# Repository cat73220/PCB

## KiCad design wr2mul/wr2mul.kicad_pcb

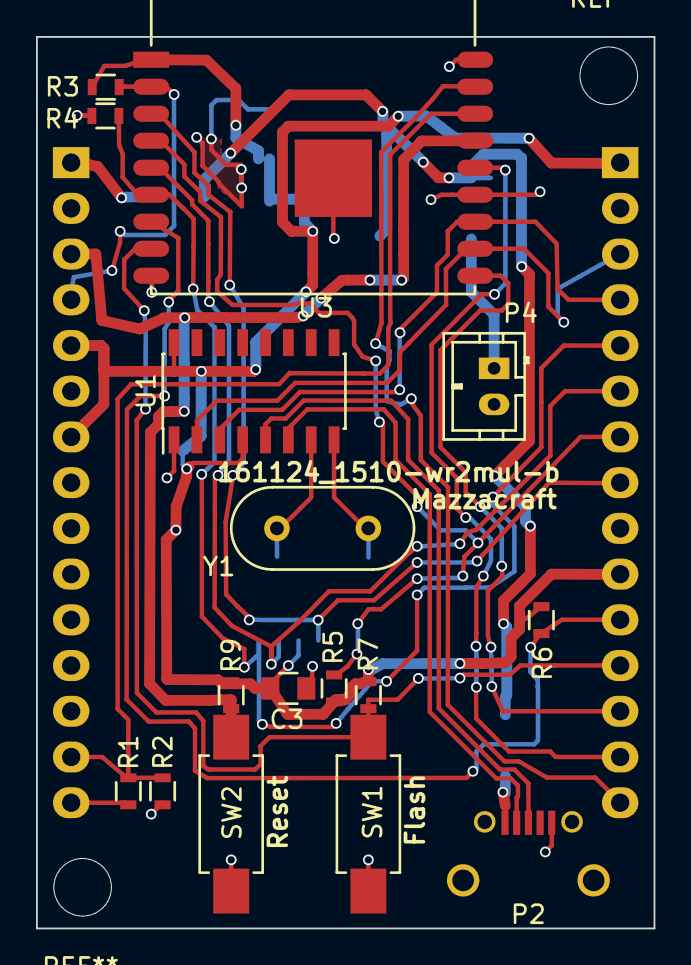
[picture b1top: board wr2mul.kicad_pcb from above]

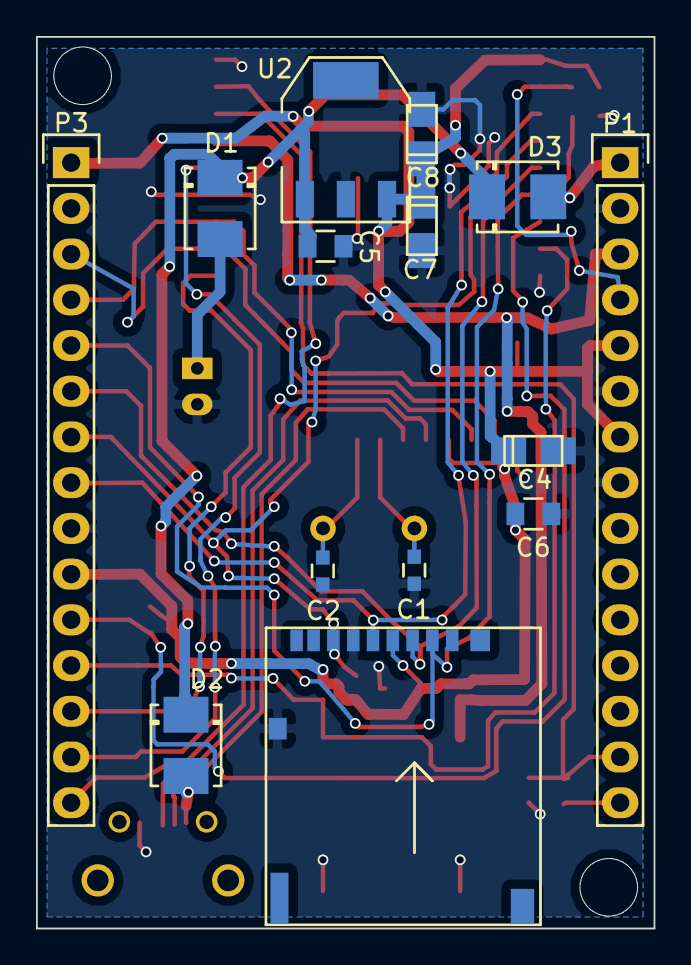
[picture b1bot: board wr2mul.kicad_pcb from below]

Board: 2 copper layers, 34.3 x 49.5 mm, 30 parts (14 on the bottom side), 25 nets.

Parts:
C1, C2: 22; C_0603
C3, C6: 10u; C_0805
C4, C8: 100u; TantalC_SizeS_EIA-3216
C5: 0.47u; C_0805
C7: 47u; TantalC_SizeS_EIA-3216
CON1: Micro_SD_Card; MICROSD
D1, D2, D3: IN4007/M7(DO-214AC); DO-214BA
P1, P3: THT_Male_P_1x15; Pin_Header_Straight_1x15
P2: USB_A; uUSB_B_Receptacle
P4: POWER_5V; JST_PH_B2B-PH-K_02x2.00mm_Straight
R1: 220K(1%); R_0603
R2: 100K(1%); R_0603
R3, R4, R5, R6, R7, R9: 10K; R_0603
SW1: Flash; SW_SPST_REED_CT05-XXXX-G1
SW2: Reset; SW_SPST_REED_CT05-XXXX-G1
U1: CH340G; SOIC-16_3.9x9.9mm_Pitch1.27mm
U2: LM3940IMP-3.3; SOT-223
U3: ESP-13-WROOM-02
Y1: 12MHz; HC-49V

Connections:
+5V: D1.2, P4.1
/ADC: P1.14, R1.2, R2.2, U3.16
/EN: P1.4, R3.2, U3.2
/GPIO0: P3.12, R7.2, SW1.2, U3.8
/GPIO2: P3.11, R6.2, U3.7
/GPIO4: P3.13, U3.10
/GPIO5: P3.14, U3.14
/GPIO12: CON1.7, P3.7, R5.2, U3.4
/GPIO13: CON1.3, P3.6, U3.5
/GPIO14: CON1.5, P3.8, U3.3
/GPIO15: CON1.2, P3.5, R4.1, U3.6
/GPIO16: P3.15, U3.17
/RS232_RX: P3.4, U1.3, U3.12
/RS232_TX: P3.3, U1.2, U3.11
/USB_D+: P2.3, U1.5
/USB_D-: P2.2, U1.6
/nRST: P1.3, R9.2, SW2.2, U3.15
GND: C1.2, C2.2, C3.2, C4.2, C5.1, C6.2, C7.2, C8.2, CON1.6, CON1.9, P1.2, P1.6, P1.8, P2.5, P3.2, P3.9, P4.2, R2.1, R4.2, SW1.1, SW2.1, U1.1, U2.2, U3.9, U3.13, U3.18, U3.PAD
unnamed: C1.1, U1.7, Y1.1
unnamed: C2.1, U1.8, Y1.2
unnamed: D3.2, P1.1
unnamed: P1.15, R1.1
VCC: C3.1, C4.1, C6.1, C7.1, C8.1, CON1.4, P1.5, P1.7, P3.1, P3.10, R3.1, R5.1, R6.1, R7.1, R9.1, U1.4, U1.16, U2.3, U3.1
VCOM: D2.2, P2.1
VDD: C5.2, D1.1, D2.1, D3.1, U2.1

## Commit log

2016-08-25 Added WROOM02-SDCard design
2016-08-25 PCB Artworking is progressing.
2016-08-26 PCB Artworking is progressing..
2016-08-30 PCB Artworking the first is done.
2016-08-31 CH340G Placement test crossing on sdcard receptacle
2016-08-31 Testing done.
2016-08-31 Satisfy design
2016-08-31 Made BOM
2016-09-02 Footprint was fit in to the ordered parts
2016-09-02 Checked before PCB order
